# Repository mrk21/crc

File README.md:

crc
===

Canon Kiss X5 Remote Controller. This device makes it possible to record movie continuously.

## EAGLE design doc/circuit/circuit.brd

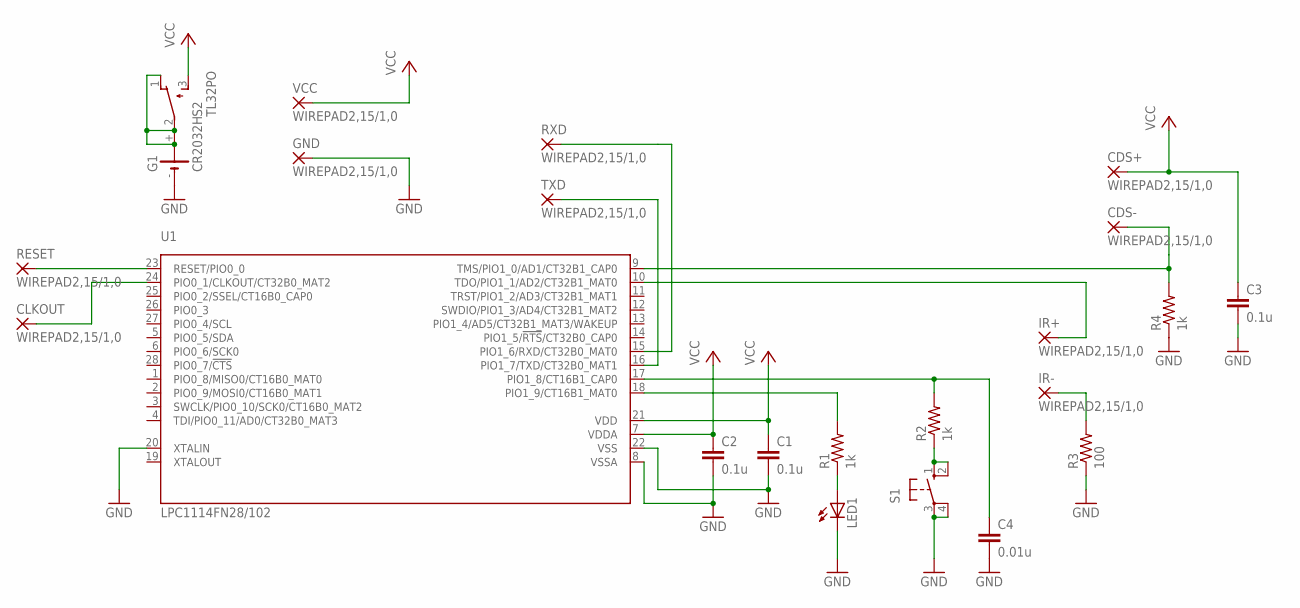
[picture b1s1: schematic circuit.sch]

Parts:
C1, C2, C3: 0.1u; C025-024X044
C4: 0.01u; C025-024X044
CDS+: WIREPAD2,15/1,0; 2,15/1,0
CDS-: WIREPAD2,15/1,0; 2,15/1,0
CLKOUT: WIREPAD2,15/1,0; 2,15/1,0
G1: CR2032H
GND: WIREPAD2,15/1,0; 2,15/1,0
IR+: WIREPAD2,15/1,0; 2,15/1,0
IR-: WIREPAD2,15/1,0; 2,15/1,0
LED1: LED5MM
R1, R2, R4: 1k; 0204/7
R3: 100; 0204/7
RESET: WIREPAD2,15/1,0; 2,15/1,0
RXD: WIREPAD2,15/1,0; 2,15/1,0
S1: 10-XX; B3F-10XX
S2: TL32PO; TL3XPO
TXD: WIREPAD2,15/1,0; 2,15/1,0
U1: LPC1114FN28/102; SOT117
VCC: WIREPAD2,15/1,0; 2,15/1,0

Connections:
GND: C1.2, C2.2, C3.2, C4.2, G1.-, GND.1, LED1.K (C), R3.1, R4.1, S1.3, S1.4 (P1), U1.8 (VSSA), U1.20 (XTALIN), U1.22 (VSS)
GND2: TXD.1, U1.16 (PIO1_7/TXD/CT32B0_MAT1)
unnamed: IR-.1, R3.2
unnamed: R2.1, S1.1 (S), S1.2 (S1)
unnamed: RESET.1, U1.23 (RESET/PIO0_0)
unnamed: CLKOUT.1, U1.24 (PIO0_1/CLKOUT/CT32B0_MAT2)
unnamed: G1.+, G1.+@1 (+), S2.1 (O), S2.2
unnamed: R1.2, U1.18 (PIO1_9/CT16B1_MAT0)
unnamed: C4.1, R2.2, U1.17 (PIO1_8/CT16B1_CAP0)
unnamed: LED1.A, R1.1
unnamed: CDS-.1, R4.2, U1.9 (TMS/PIO1_0/AD1/CT32B1_CAP0)
VCC: C1.1, C2.1, C3.1, CDS+.1, S2.3 (S), U1.7 (VDDA), U1.21 (VDD), VCC.1
VCC1: IR+.1, U1.10 (TDO/PIO1_1/AD2/CT32B1_MAT0)
VCC3: RXD.1, U1.15 (PIO1_6/RXD/CT32B0_MAT0)

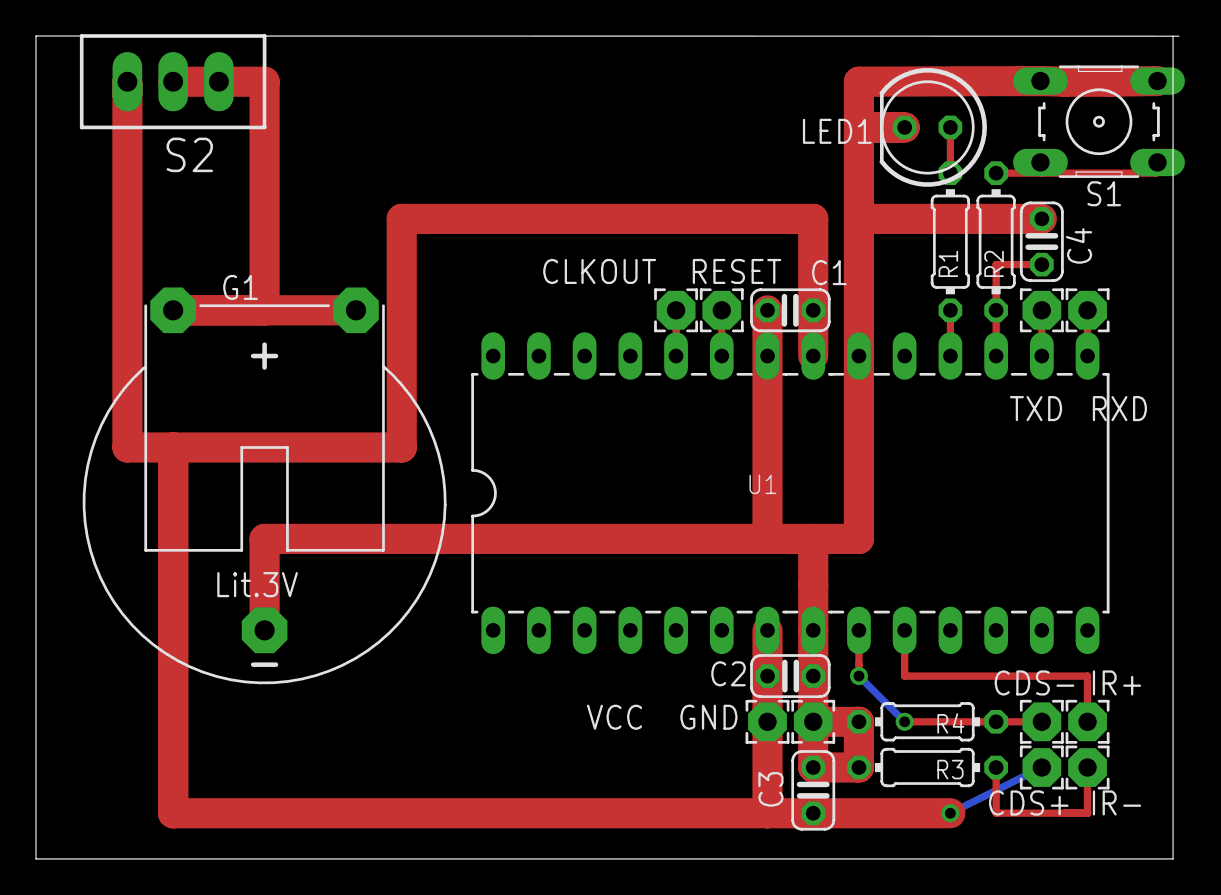
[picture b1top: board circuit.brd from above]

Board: 2 copper layers, 63.5 x 45.7 mm, 23 parts (0 on the bottom side), 14 nets.

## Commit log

2013-07-31 initialized.
2013-08-08 fixes #189.
2013-08-09 fixes #191, #192.
2013-10-03 fixes #206.
2013-10-07 fixes #210.
2015-03-28 Added docs.
2015-03-28 Create LICENSE
2015-03-28 Added captures.
2015-03-28 Updated README.md.
